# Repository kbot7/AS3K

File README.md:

# The Mechanical AlphaSmart 3000
This is a hardware mod for the AlphaSmart 3000 that swaps the keyboard out for a mechanical one.

The revisions here have compatibility issues and are deprecated. Information on the most recent revision is available [here](https://tilde.club/~jy4m/alphasmart).

## kbot's dev goals
- [ ] Update to latest KiCad
- [ ] Update footprint and symbol libraries
- [ ] Support hot-swap sockets
- [ ] Support LEDs

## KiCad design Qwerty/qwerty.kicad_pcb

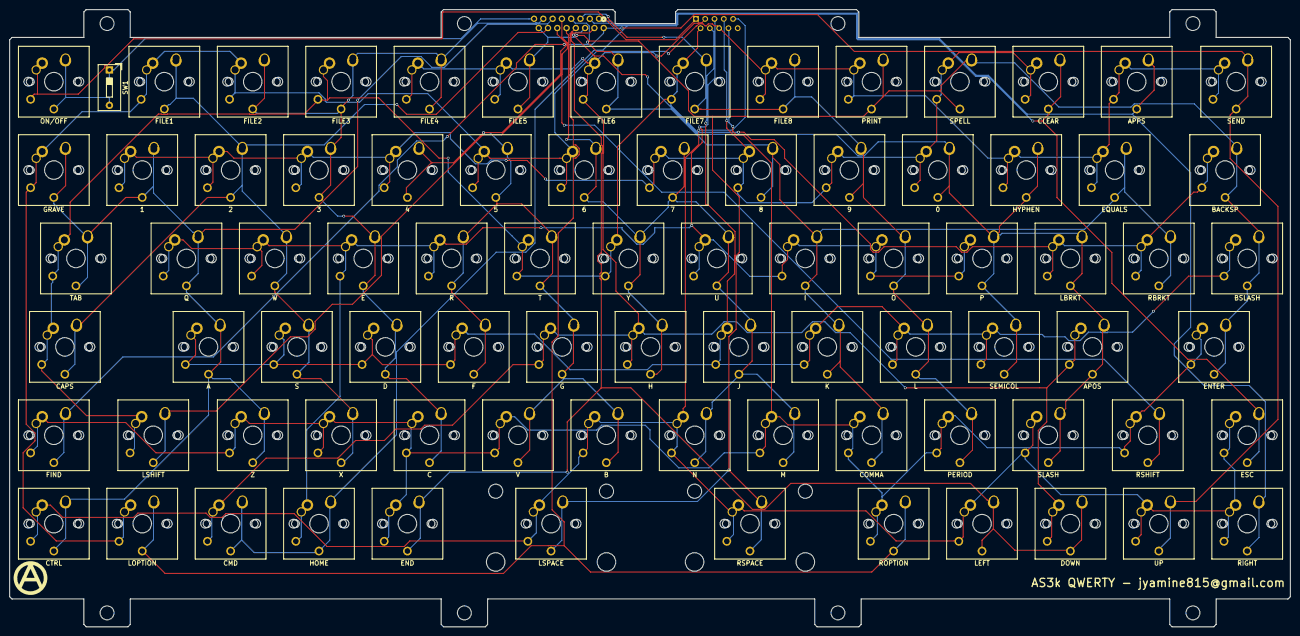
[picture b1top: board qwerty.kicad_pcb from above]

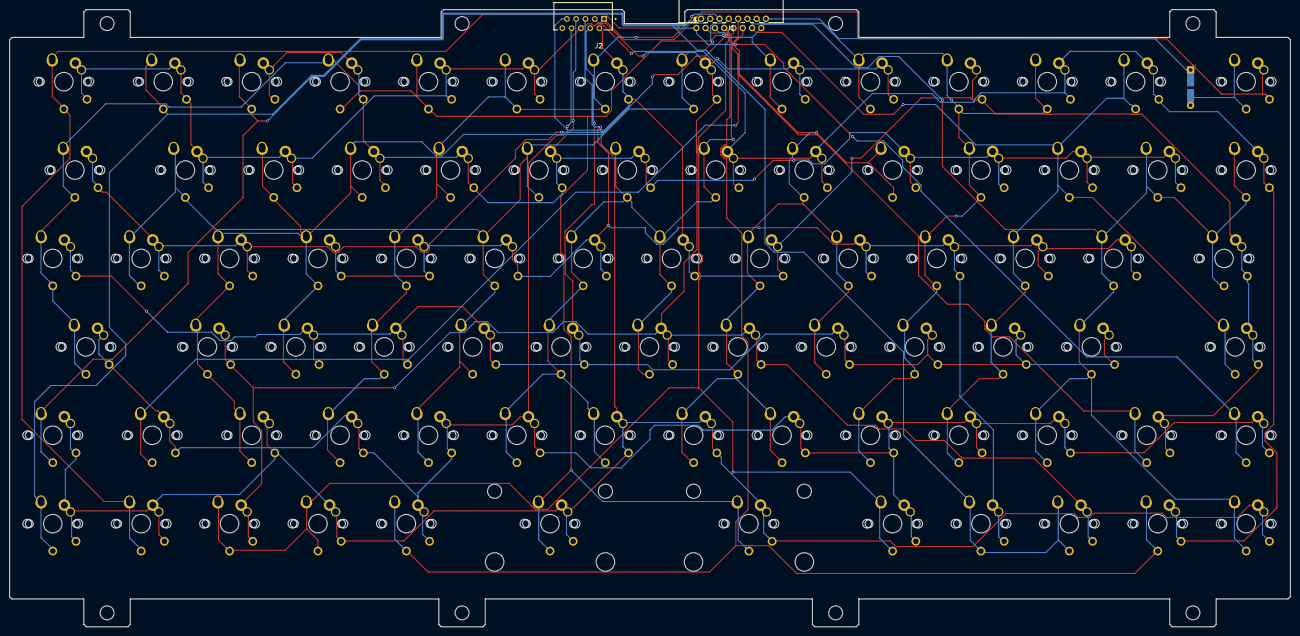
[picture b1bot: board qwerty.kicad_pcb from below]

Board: 2 copper layers, 276.0 x 133.0 mm, 84 parts (2 on the bottom side), 26 nets.

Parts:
A1: A; MX_ALPS_PG1350
APOS1: APOS; MX_ALPS_PG1350
APPS1: APPS; MX_ALPS_PG1350
B1: B; MX_ALPS_PG1350
BACKSP1: BACKSP; MX_ALPS_PG1350
BSLASH1: BSLASH; MX_ALPS_PG1350
C1: C; MX_ALPS_PG1350
CAPS1: CAPS; MX_ALPS_PG1350
CBRKT1: RBRKT; MX_ALPS_PG1350
CLEAR1: CLEAR; MX_ALPS_PG1350
CMD1: CMD; MX_ALPS_PG1350
COMMA1: COMMA; MX_ALPS_PG1350
CTRL1: CTRL; MX_ALPS_PG1350
D1: D; MX_ALPS_PG1350
DOWN1: DOWN; MX_ALPS_PG1350
E1: E; MX_ALPS_PG1350
EIGHT1: 8; MX_ALPS_PG1350
END1: END; MX_ALPS_PG1350
ENTER1: ENTER; MX_ALPS_PG1350
EQUALS1: EQUALS; MX_ALPS_PG1350
ESC1: ESC; MX_ALPS_PG1350
F1: F; MX_ALPS_PG1350
FILE1: FILE1; MX_ALPS_PG1350
FILE2: FILE2; MX_ALPS_PG1350
FILE3: FILE3; MX_ALPS_PG1350
FILE4: FILE4; MX_ALPS_PG1350
FILE5: FILE5; MX_ALPS_PG1350
FILE6: FILE6; MX_ALPS_PG1350
FILE7: FILE7; MX_ALPS_PG1350
FILE8: FILE8; MX_ALPS_PG1350
FIND1: FIND; MX_ALPS_PG1350
FIVE1: 5; MX_ALPS_PG1350
FOUR1: 4; MX_ALPS_PG1350
G1: G; MX_ALPS_PG1350
GRAVE1: GRAVE; MX_ALPS_PG1350
H1: H; MX_ALPS_PG1350
HOME1: HOME; MX_ALPS_PG1350
HYPHEN1: HYPHEN; MX_ALPS_PG1350
I1: I; MX_ALPS_PG1350
J1: Conn_01x16; CON16_1X16_RB_58JF_GLE
J2: Conn_01x10; AMPHENOL_HLW10R-2C7LF
J3: J; MX_ALPS_PG1350
K1: K; MX_ALPS_PG1350
L1: L; MX_ALPS_PG1350
LEFT1: LEFT; MX_ALPS_PG1350
LOPTION1: LOPTION; MX_ALPS_PG1350
LSHIFT1: LSHIFT; MX_ALPS_PG1350
LSPACE1: LSPACE; MX_ALPS_PG1350
M1: M; MX_ALPS_PG1350
N1: N; MX_ALPS_PG1350
NINE1: 9; MX_ALPS_PG1350
O1: O; MX_ALPS_PG1350
OBRKT1: LBRKT; MX_ALPS_PG1350
ON/OFF1: ON/OFF; MX_ALPS_PG1350
ONE1: 1; MX_ALPS_PG1350
P1: P; MX_ALPS_PG1350
PERIOD1: PERIOD; MX_ALPS_PG1350
PRINT1: PRINT; MX_ALPS_PG1350
Q1: Q; MX_ALPS_PG1350
R1: R; MX_ALPS_PG1350
RIGHT1: RIGHT; MX_ALPS_PG1350
ROPTION1: ROPTION; MX_ALPS_PG1350
RSHIFT1: RSHIFT; MX_ALPS_PG1350
RSPACE1: RSPACE; MX_ALPS_PG1350
S1: S; MX_ALPS_PG1350
SEMICOL1: SEMICOL; MX_ALPS_PG1350
SEND1: SEND; MX_ALPS_PG1350
SEVEN1: 7; MX_ALPS_PG1350
SIX1: 6; MX_ALPS_PG1350
SLASH1: SLASH; MX_ALPS_PG1350
SPELL1: SPELL; MX_ALPS_PG1350
SW1: SW_DIP_x01; SW_DIP_SPSTx01_Slide_9.78x4.72mm_W7.62mm_P2.54mm_wJumper
T1: T; MX_ALPS_PG1350
TAB1: TAB; MX_ALPS_PG1350
THREE1: 3; MX_ALPS_PG1350
TWO1: 2; MX_ALPS_PG1350
U1: U; MX_ALPS_PG1350
UP1: UP; MX_ALPS_PG1350
V1: V; MX_ALPS_PG1350
W1: W; MX_ALPS_PG1350
X1: X; MX_ALPS_PG1350
Y1: Y; MX_ALPS_PG1350
Z1: Z; MX_ALPS_PG1350
ZERO1: 0; MX_ALPS_PG1350

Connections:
/COL1: J1.16, SW1.1
/COL2: BACKSP1.1, BSLASH1.1, ENTER1.1, FILE5.1, J1.15, LSPACE1.1, PRINT1.1, RSPACE1.1, SPELL1.1
/COL3: C1.1, D1.1, E1.1, FILE2.1, FILE3.1, FILE4.1, J1.14, THREE1.1
/COL4: CAPS1.1, FILE1.1, J1.13, S1.1, TWO1.1, W1.1, X1.1
/COL5: A1.1, CTRL1.1, GRAVE1.1, J1.12, ONE1.1, Q1.1, TAB1.1, Z1.1
/COL6: B1.1, F1.1, FIVE1.1, FOUR1.1, G1.1, J1.11, R1.1, T1.1, V1.1
/COL7: J1.10, LSHIFT1.1, RSHIFT1.1
/COL8: H1.1, J1.9, J3.1, M1.1, N1.1, SEVEN1.1, SIX1.1, U1.1, Y1.1
/COL9: CBRKT1.1, COMMA1.1, EIGHT1.1, EQUALS1.1, FILE6.1, I1.1, J1.8, K1.1
/COL10: J1.7, LOPTION1.1, ROPTION1.1
/COL11: FILE7.1, FILE8.1, J1.6, L1.1, NINE1.1, O1.1, PERIOD1.1
/COL12: APOS1.1, HYPHEN1.1, J1.5, OBRKT1.1, P1.1, SEMICOL1.1, SLASH1.1, ZERO1.1
/COL13: CLEAR1.1, CMD1.1, ESC1.1, HOME1.1, J1.4
/COL14: DOWN1.1, END1.1, J1.3, LEFT1.1
/COL15: APPS1.1, J1.2, RIGHT1.1
/COL16: FIND1.1, J1.1, SEND1.1, UP1.1
/ROW1: J2.1, ON/OFF1.2
/ROW2: BACKSP1.2, CAPS1.2, CBRKT1.2, FILE3.2, FILE7.2, J2.2, LSHIFT1.2, OBRKT1.2, T1.2, TAB1.2, Y1.2
/ROW3: APOS1.2, CMD1.2, DOWN1.2, FILE4.2, FILE5.2, FILE6.2, G1.2, H1.2, J2.3
/ROW4: A1.2, BSLASH1.2, D1.2, F1.2, J2.4, J3.2, K1.2, L1.2, S1.2, SEMICOL1.2
/ROW5: E1.2, HOME1.2, I1.2, J2.5, O1.2, P1.2, Q1.2, R1.2, U1.2, W1.2
/ROW6: APPS1.2, EQUALS1.2, FILE1.2, FILE2.2, FILE8.2, FIVE1.2, GRAVE1.2, HYPHEN1.2, J2.6, LOPTION1.2, PRINT1.2, SEND1.2, SIX1.2
/ROW7: CLEAR1.2, EIGHT1.2, FOUR1.2, J2.7, NINE1.2, ONE1.2, SEVEN1.2, SPELL1.2, THREE1.2, TWO1.2, ZERO1.2
/ROW8: C1.2, COMMA1.2, END1.2, ENTER1.2, FIND1.2, J2.8, M1.2, PERIOD1.2, ROPTION1.2, RSHIFT1.2, V1.2, X1.2, Z1.2
/ROW9: B1.2, CTRL1.2, ESC1.2, J2.9, LEFT1.2, LSPACE1.2, N1.2, RIGHT1.2, RSPACE1.2, SLASH1.2, UP1.2
unnamed: ON/OFF1.1, SW1.2

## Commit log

2024-08-17 Added qwerty layout project from web
    Added files from tilde.club to 'qwerty' folder from: https://tilde.club/~jy4m/alphasmart/project_files/qwerty/qwerty.zip
2024-08-17 Updated kicad and gerbers to latest version of kicad
2024-08-17 Updated connector libraries
2024-08-17 Setup 3D models on PCB for connectors
2024-08-17 Updated connector footprint on PCB
